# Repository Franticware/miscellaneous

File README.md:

This repository contains various stuff related to other projects

### Misc. docs:
https://franticware.github.io/miscellaneous/

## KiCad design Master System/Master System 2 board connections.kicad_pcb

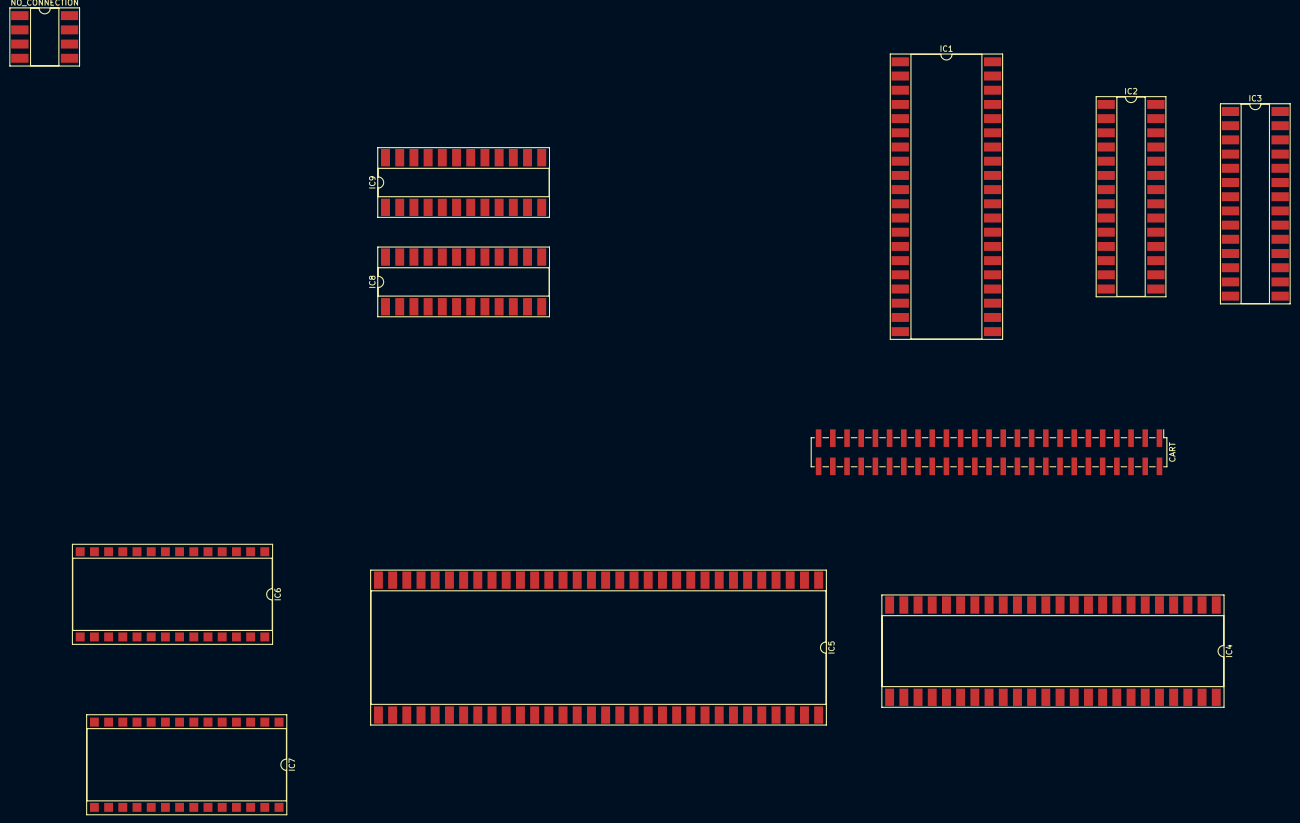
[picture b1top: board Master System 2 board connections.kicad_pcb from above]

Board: 2 copper layers, 11 parts (0 on the bottom side), 69 nets, no tracks yet.

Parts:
CART: PinHeader_2x25_P2.54mm_Vertical_SMD
IC1: DIP-40_W16.51mm_SMDSocket_LongPads
IC2, IC3: DIP-28_W8.89mm_SMDSocket_LongPads
IC4: DIP-48_W16.51mm_SMDSocket_LongPads
IC5: DIP-64_W24.13mm_SMDSocket_LongPads
IC6, IC7: DIP-28_W15.24mm_SMDSocket_SmallPads
IC8, IC9: DIP-24_W8.89mm_SMDSocket_LongPads
NO_CONNECTION: DIP-8_W8.89mm_SMDSocket_LongPads

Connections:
Net-10m7: IC4.41, IC5.35
Net-a0: CART.25, IC1.30, IC2.10, IC3.10, IC4.2, IC5.61
Net-a1: CART.26, IC1.31, IC2.9, IC3.9
Net-a2: CART.27, IC1.32, IC2.8, IC3.8
Net-a3: CART.28, IC1.33, IC2.7, IC3.7
Net-a4: CART.29, IC1.34, IC2.6, IC3.6
Net-a5: CART.30, IC1.35, IC2.5, IC3.5
Net-a6: CART.31, IC1.36, IC2.4, IC3.4, IC4.3, IC5.62
Net-a7: CART.32, IC1.37, IC2.3, IC3.3, IC4.4, IC5.63
Net-a8: CART.8, IC1.38, IC2.25, IC3.25
Net-a9: CART.9, IC1.39, IC2.24, IC3.24
Net-a10: CART.12, IC1.40, IC2.21, IC3.21
Net-a11: CART.10, IC1.1, IC2.23, IC3.23
Net-a12: CART.33, IC1.2, IC2.2, IC3.2
Net-a13: CART.7, IC1.3, IC2.26
Net-a14: CART.6, IC1.4, IC2.27, IC5.13
Net-a15: CART.36, IC1.5, IC5.19
Net-ad0: IC5.41, IC6.10, IC6.11, IC7.10
Net-ad1: IC5.42, IC6.9, IC6.12, IC7.9
Net-ad2: IC5.43, IC6.8, IC6.13, IC7.8
Net-ad3: IC5.44, IC6.7, IC6.15, IC7.7
Net-ad4: IC5.45, IC6.6, IC6.16, IC7.6
Net-ad5: IC5.46, IC6.5, IC6.17, IC7.5
Net-ad6: IC5.47, IC6.4, IC6.18, IC7.4
Net-ad7: IC5.48, IC6.3, IC6.19, IC7.3
Net-ad8: IC5.49, IC6.25, IC7.11, IC7.25
Net-ad9: IC5.50, IC6.24, IC7.12, IC7.24
Net-ad10: IC5.51, IC6.21, IC7.13, IC7.21
Net-ad11: IC5.52, IC6.23, IC7.15, IC7.23
Net-ad12: IC5.53, IC6.2, IC7.2, IC7.16
Net-ad13: IC5.54, IC7.17
Net-ad14: IC5.55, IC7.18
Net-ad15: IC5.56, IC7.19
Net-busak: CART.45, IC1.23
Net-ce1: IC3.20, IC4.38
Net-ce3: CART.13, IC4.36
Net-ce_vram: IC5.39, IC6.20, IC7.20
Net-clock: CART.47, IC5.33
Net-csram: CART.49, IC4.9, IC5.10
Net-d0: CART.24, IC1.14, IC2.11, IC3.11, IC4.32, IC5.1
Net-d1: CART.23, IC1.15, IC2.12, IC3.12, IC4.31, IC5.2
Net-d2: CART.22, IC1.12, IC2.13, IC3.13, IC4.30, IC5.3
Net-d3: CART.18, IC1.8, IC2.15, IC3.15, IC4.29, IC5.4
Net-d4: CART.17, IC1.7, IC2.16, IC3.16, IC4.28, IC5.5
Net-d5: CART.16, IC1.9, IC2.17, IC3.17, IC4.27, IC5.6
Net-d6: CART.15, IC1.10, IC2.18, IC3.18, IC4.26, IC5.7
Net-d7: CART.14, IC1.13, IC2.19, IC3.19, IC4.25, IC5.8
Net-exm1: CART.5, IC5.11
Net-exm2: CART.11, IC2.22, IC5.12
Net-gnd: CART.19, CART.20, CART.21, IC1.29, IC2.14, IC3.14, IC4.24, IC4.40, IC5.18, IC5.32, IC6.14, IC7.14
Net-halt: CART.40, IC1.18
Net-hl: IC4.34, IC5.24
Net-int: CART.42, IC1.16, IC5.64
Net-ioreq: CART.38, IC4.7, IC5.60
Net-kbsel: CART.48, IC5.9
Net-killga: CART.43, IC4.1
Net-m1: CART.37, IC1.27
Net-mreq: CART.3, IC1.19, IC2.20, IC4.8, IC5.20
Net-nmi_in: IC5.21, IC5.22
Net-oe_vram: IC5.38, IC6.22, IC7.22
Net-rd: CART.4, IC1.21, IC4.6, IC5.58
Net-refsh: CART.39, IC1.28
Net-reset: CART.46, IC1.26, IC4.46, IC5.23
Net-sync: IC4.45, IC5.30
Net-vcc: CART.1, CART.35, IC1.11, IC2.28, IC3.26, IC3.28, IC4.48, IC5.17, IC5.40, IC6.1, IC6.26, IC6.28, IC7.1, IC7.26, IC7.28
Net-wait: CART.41, IC1.24
Net-we0: IC5.37, IC6.27
Net-we1: IC5.36, IC7.27
Net-wr: CART.2, IC1.22, IC2.1, IC3.22, IC4.5, IC5.59

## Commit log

2021-02-05 Added mddumper.rules
2021-02-05 Fix for Sega_Dumper software
2021-02-05 Patch for the current official Sega_Dumper main.c
2021-05-03 Rename FlashKit-MD-SRAM.md to README.md
2022-06-16 new directory
2022-06-26 Quake 2 save
2022-10-18 Misc. web page listing
    OPL3 docs
2022-10-19 Added missing images; adlib guide
2023-08-19 Added screenshot from the original Quake II
2023-08-22 Master System 2 board continuity
2023-08-22 kicad_pcb reformat
2024-10-05 Add perlin noise implementation in C/C++ (rewritten from Java)
2025-11-23 Add fix for "WCH-Link not found"
